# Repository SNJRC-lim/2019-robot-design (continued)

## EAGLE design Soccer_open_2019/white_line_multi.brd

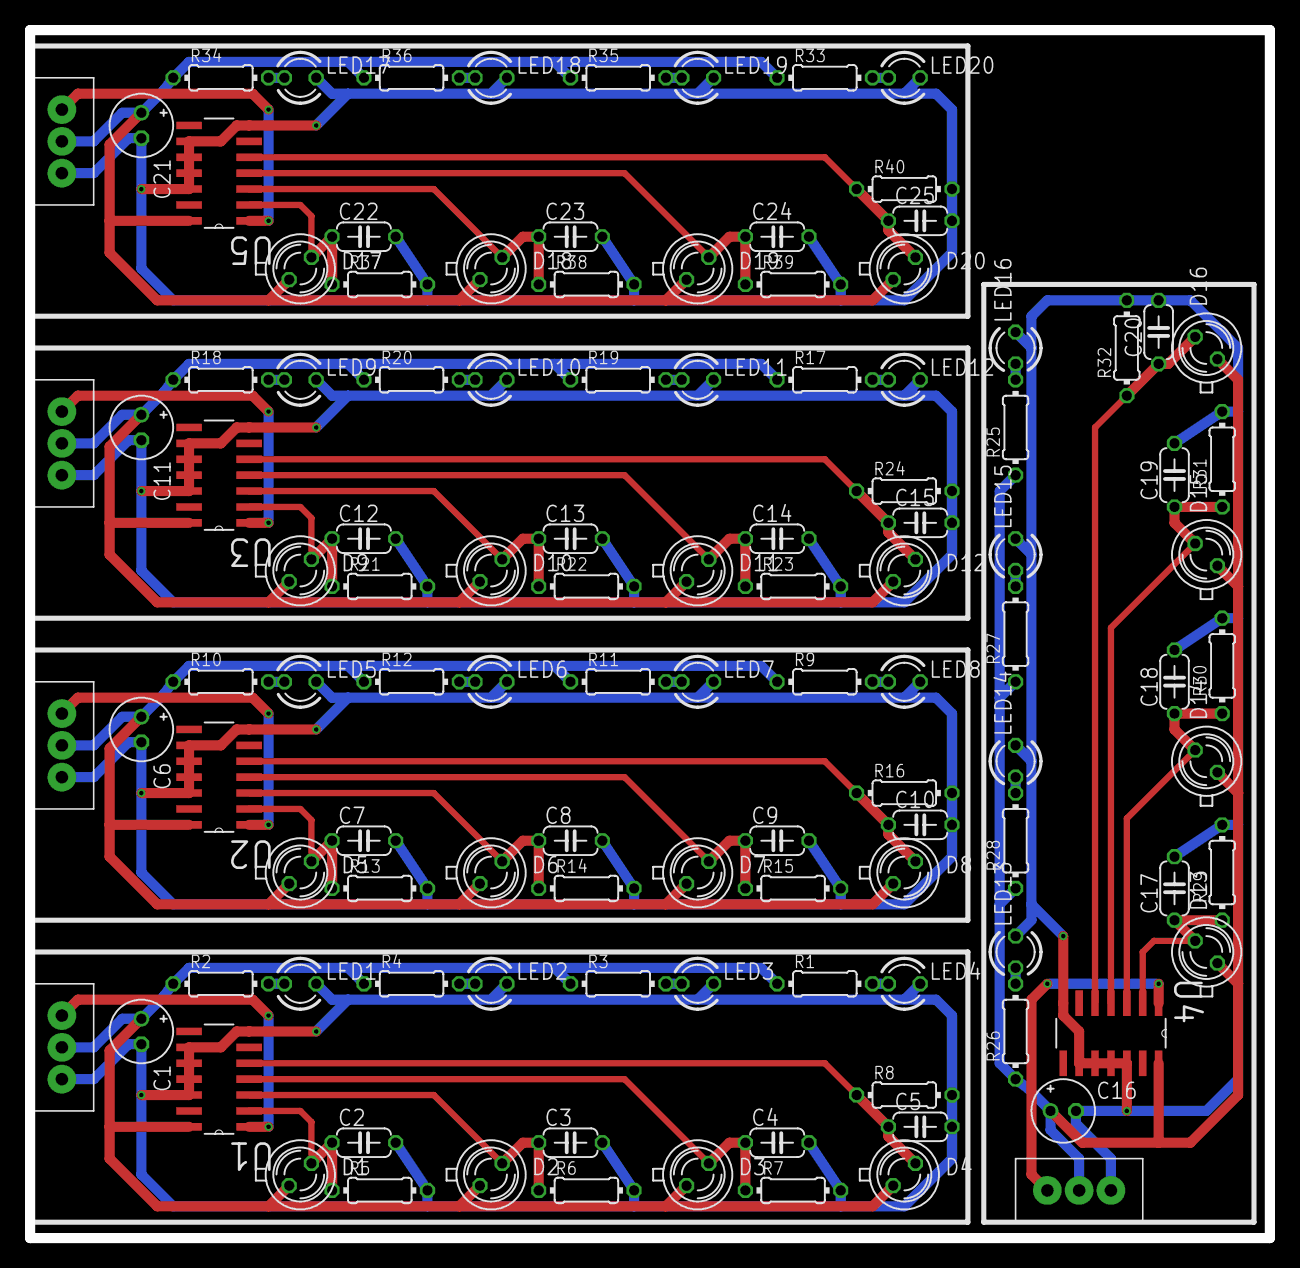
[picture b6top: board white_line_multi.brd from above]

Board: 2 copper layers, 99.1 x 96.5 mm, 115 parts (0 on the bottom side), 47 nets.

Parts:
3PIN1, 3PIN2, 3PIN3, 3PIN4, 3PIN5: 3PIN
C1, C6, C11, C16, C21: E2-5
C2, C3, C4, C5, C7, C8, C9, C10, C12, C13, C14, C15, C17, C18, C19, C20, C22, C23, C24, C25: C050-024X044
D1, D2, D3, D4, D5, D6, D7, D8, D9, D10, D11, D12, D13, D14, D15, D16, D17, D18, D19, D20: BPX65
LED1, LED2, LED3, LED4, LED5, LED6, LED7, LED8, LED9, LED10, LED11, LED12, LED13, LED14, LED15, LED16, LED17, LED18, LED19, LED20: LED3MM
R1, R2, R3, R4, R5, R6, R7, R8, R9, R10, R11, R12, R13, R14, R15, R16, R17, R18, R19, R20, R21, R22, R23, R24, R25, R26, R27, R28, R29, R30, R31, R32, R33, R34, R35, R36, R37, R38, R39, R40: 0204/7
U1, U2, U3, U4, U5: CD4072BM; SOIC127P600X175-14N

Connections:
A: C2.1, D1.K, R5.1, U1.2
A1: C7.1, D5.K, R13.1, U2.2
A2: C12.1, D9.K, R21.1, U3.2
A3: C17.1, D13.K, R29.1, U4.2
A4: C22.1, D17.K, R37.1, U5.2
B: C3.1, D2.K, R6.1, U1.3
B1: C8.1, D6.K, R14.1, U2.3
B2: C13.1, D10.K, R22.1, U3.3
B3: C18.1, D14.K, R30.1, U4.3
B4: C23.1, D18.K, R38.1, U5.3
C: C4.1, D3.K, R7.1, U1.4
C1: C9.1, D7.K, R15.1, U2.4
C2: C14.1, D11.K, R23.1, U3.4
C3: C19.1, D15.K, R31.1, U4.4
C4: C24.1, D19.K, R39.1, U5.4
D: C5.1, D4.K, R8.1, U1.5
D1: C10.1, D8.K, R16.1, U2.5
D2: C15.1, D12.K, R24.1, U3.5
D3: C20.1, D16.K, R32.1, U4.5
D4: C25.1, D20.K, R40.1, U5.5
GND: 3PIN1.P$3, 3PIN2.P$3, 3PIN3.P$3, 3PIN4.P$3, 3PIN5.P$3, C1.-, C2.2, C3.2, C4.2, C5.2, C6.-, C7.2, C8.2, C9.2, C10.2, C11.-, C12.2, C13.2, C14.2, C15.2, C16.-, C17.2, C18.2, C19.2, C20.2, C21.-, C22.2, C23.2, C24.2, C25.2, LED1.K, LED2.K, LED3.K, LED4.K, LED5.K, LED6.K, LED7.K, LED8.K, LED9.K, LED10.K, LED11.K, LED12.K, LED13.K, LED14.K, LED15.K, LED16.K, LED17.K, LED18.K, LED19.K, LED20.K, R5.2, R6.2, R7.2, R8.2, R13.2, R14.2, R15.2, R16.2, R21.2, R22.2, R23.2, R24.2, R29.2, R30.2, R31.2, R32.2, R37.2, R38.2, R39.2, R40.2, U1.7, U1.9, U1.10, U1.11, U1.12, U2.7, U2.9, U2.10, U2.11, U2.12, U3.7, U3.9, U3.10, U3.11, U3.12, U4.7, U4.9, U4.10, U4.11, U4.12, U5.7, U5.9, U5.10, U5.11, U5.12
unnamed: LED4.A, R1.2
unnamed: LED1.A, R2.2
unnamed: LED3.A, R3.2
unnamed: LED2.A, R4.2
unnamed: LED8.A, R9.2
unnamed: LED5.A, R10.2
unnamed: LED7.A, R11.2
unnamed: LED6.A, R12.2
unnamed: LED12.A, R17.2
unnamed: LED9.A, R18.2
unnamed: LED11.A, R19.2
unnamed: LED10.A, R20.2
unnamed: LED16.A, R25.2
unnamed: LED13.A, R26.2
unnamed: LED15.A, R27.2
unnamed: LED14.A, R28.2
unnamed: LED20.A, R33.2
unnamed: LED17.A, R34.2
unnamed: LED19.A, R35.2
unnamed: LED18.A, R36.2
OUT: 3PIN2.P$1, U1.1
OUT1: 3PIN1.P$1, U2.1
OUT2: 3PIN3.P$1, U3.1
OUT3: 3PIN4.P$1, U4.1
OUT4: 3PIN5.P$1, U5.1
VCC: 3PIN1.P$2, 3PIN2.P$2, 3PIN3.P$2, 3PIN4.P$2, 3PIN5.P$2, C1.+, C6.+, C11.+, C16.+, C21.+, D1.A, D2.A, D3.A, D4.A, D5.A, D6.A, D7.A, D8.A, D9.A, D10.A, D11.A, D12.A, D13.A, D14.A, D15.A, D16.A, D17.A, D18.A, D19.A, D20.A, R1.1, R2.1, R3.1, R4.1, R9.1, R10.1, R11.1, R12.1, R17.1, R18.1, R19.1, R20.1, R25.1, R26.1, R27.1, R28.1, R33.1, R34.1, R35.1, R36.1, U1.14, U2.14, U3.14, U4.14, U5.14

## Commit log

2019-12-21 upload README.md
2019-12-21 upload circuit bord
